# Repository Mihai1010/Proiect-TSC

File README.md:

# Proiect InkTime

**Autor:** Necula Mihai 331 AB

---

## 1. Diagramă Bloc

---

## 2. Bill of Materials (BOM)

| Categorie | Capsulă | Denumire Schematic | JLC | Datasheet |
| :--- | :--- | :--- | :--- | :--- |
| **Capacitors** | **0201** | C1, C2, C3, C4, C5, C7, C8, C9, C11, C12, C13, C16, C17, C18, C19, C22, C23, C27, C29, C30, C31, C32, C34, C37, C38, C42, EPD_C5 | [JLCPCB](https://jlcpcb.com/partdetail/16204-CL05A106MQ5NUNC/C15525) | [DataSheet](https://www.jotrin.jp/userfiles/downloadfile/CL05A106MQ5NUNC/CL05A106MQ5NUNC.pdf) |
| | **0402** | C6, C14, C15, C20, C21, C24, C25, C33, C39, C43, EPD_C1, EPD_C2, EPD_C6, EPD_C7, EPD_C8, EPD_C9, EPD_C10, EPD_C11, EPD_C12, C2-EP-DR1 | [JLCPCB](https://jlcpcb.com/partdetail/C9900006337) | [DataSheet](https://jlcpcb.com/parts) |
| **Resistors** | **0201** | R2, R3, R4, R5, R7, R8, R9, R17, R18, R_TYPE_SEL, R1_EP_DR, R2_EP_DR, R2_PWR_EPD, R1_USB, R2_USB | [JLCPCB](https://jlcpcb.com/partdetail/26484-0402WGF1003TCE/C25741) | [DataSheet](https://www.royalohm.com/assets/pdf/products/smd/1.pdf) |
| **Inductors** | **0402** | L1, L2, L3 | [JLCPCB](https://jlcpcb.com/partdetail/6763488-FTC252012SR47MBCA/C5832368) | [DataSheet](https://www.lcsc.com/datasheet/C5832368.pdf) |
| | **SMD** | L5, L7 | [JLCPCB](https://jlcpcb.com/partdetail/Walsin_TechCorp-WR06X60R4FTL/C168340) | [DataSheet](https://eu.mouser.com/datasheet/3/317/1/ASC_WR.pdf) |
| **ICs** | **BGA/WLCSP** | U1 (nRF52840) | [JLCPCB](https://jlcpcb.com/partdetail/NordicSemicon-NRF52840_QIAAR/C190794) | [DataSheet](https://mm.digikey.com/Volume0/opasdata/d220001/medias/docus/6470/NRF52840-QIAA-R.pdf) |
| | **BGA/WLCSP** | IC1 (BQ25180YBGR) | [JLCPCB](https://jlcpcb.com/partdetail/TexasInstruments-BQ25180YBGR/C3682423) | [DataSheet](https://www.ti.com/cn/lit/ds/symlink/bq25180.pdf?ts=1776165850601) |
| | **BGA/WLCSP** | IC2 (DRV2605YZFR) | [JLCPCB](https://jlcpcb.com/partdetail/TexasInstruments-DRV2605YZFR/C81079) | [DataSheet](https://www.ti.com/cn/lit/ds/symlink/drv2605.pdf?ts=1776155639464&ref_url=https%253A%252F%252Fso.szlcsc.com%252F) |
| | **BGA/WLCSP** | IC9 (RT6160AWSC) | [JLCPCB](https://jlcpcb.com/partdetail/RichtekTech-RT6160AWSC/C7065276) | [DataSheet](https://www.alldatasheet.com/datasheet-pdf/pdf/1709403/RICHTEK/RT6160AWSC.html) |
| | **LGA** | IC3 (BMA421) | [JLCPCB](https://jlcpcb.com/partdetail/BoschSensortec-BMA421/C5242966) | [DataSheet](https://www.alldatasheet.com/datasheet-pdf/pdf/1137426/BOSCH/BMA421.html) |
| | **SON/TDFN** | U3 (MAX17048) | [JLCPCB](https://jlcpcb.com/partdetail/2777647-MAX17048GT10/C2682616) | [DataSheet](https://www.analog.com/media/en/technical-documentation/data-sheets/MAX17048-MAX17049.pdf) |
| **Diodes/FETs** | **SOD-123** | D2, D4, D5 | [JLCPCB](https://jlcpcb.com/partdetail/ST_Semtech-1N4148W/C81598) | [DataSheet](https://www.mccsemi.com/pdf/Products/1N4148W(SOD-123).pdf) |
| | **SOT-23** | Q1 (DMG2305) | [JLCPCB](https://jlcpcb.com/partdetail/TECHPUBLIC-DMG2305UX/C2940629) | [DataSheet](https://www.mouser.com/datasheet/2/115/DMG2305UX-266242.pdf) |
| | **SOT-323** | Q3 (SI1308EDL) | [JLCPCB](https://jlcpcb.com/partdetail/VishayIntertech-SI1308EDL_T1GE3/C469327) | [DataSheet](https://www.vishay.com](https://www.vishay.com/docs/63399/si1308edl.pdf)) |
| | **SOT-23-6** | D3 (USBLC6) | [JLCPCB](https://jlcpcb.com/partdetail/STMicroelectronics-USBLC62SC6/C7519) | [DataSheet](https://www.st.com](https://www.st.com/resource/en/datasheet/usblc6-2.pdf)) |
| **Connectors** | **FPC 24** | J1 | [JLCPCB](https://jlcpcb.com/partdetail/MOLEX-5034802400/C122434) | [DataSheet](https://www.molex.com/content/dam/molex/molex-dot-com/products/automated/en-us/salesdrawingpdf/503/503480/5034802400_sd.pdf?inline) |
| | **USB-C** | J4 | [JLCPCB](https://jlcpcb.com/partdetail/EverlightElec-16_213SDRC_S530_A3TR8/C71911) | [DataSheet](https://www.endrich.com/Datenbl%C3%A4tter/Lichtl%C3%B6sungen/Everlight/Single%20Color%20LED/16-213SDRCS530-A3TR8.pdf) |
| | **Tag-Connect**| J2 (TC2030) | [JLCPCB](https://jlcpcb.com/partdetail/MicrochipTech-TC2030_CLIP3PACK/C5444772) | [DataSheet](https://www.farnell.com/datasheets/2818736.pdf) |
| **User I/O** | **Switch** | SW_DN, SW_ENT, SW_UP | [JLCPCB](https://jlcpcb.com/partdetail/ALPSALPINE-SKRKAEE020/C115357) | [DataSheet](https://www.tme.eu/Document/305984bf119cfa40f7a209117dc97838/SKRKAEE020.PDF) |
| | **Antenna** | ANT1 | [JLCPCB](https://jlcpcb.com/partdetail/JohansonDielectrics-2450AT18B100E/C2917717) | [DataSheet](https://www.johansontechnology.com/docs/1187/2450AT18B100_X8XXogU.pdf) |
| | **Oscillator** | X1, X2 | [JLCPCB](https://jlcpcb.com/partdetail/STMicroelectronics-BALNRF01D3/C87765) | [DataSheet](https://www.st.com/resource/en/datasheet/bal-nrf01d3.pdf) |
| **Mechanical** | **Custom** | Baterie, Display, Shaker | - | [Mechanical Folder](./Mechanical) |

---

## 3. Descrierea Funcționalității Hardware

### 3.1 Unitatea Centrală de Procesare (MCU)
Nucleul dispozitivului este **Nordic nRF52840**. 
* Dispune de un procesor pe 32 de biți la 64 MHz, capabil să gestioneze algoritmi complecși și procesare de semnal.
* Utilizează un oscilator de **32 MHz** pentru operarea nucleului și a radioului.

### 3.2 Energie și Alimentare
* **LiPo Charger (BQ25180):** Gestionează procesul de încărcare al bateriei de 250mAh prin interfața USB-C.
* **Fuel Gauge (MAX17048):** Oferă monitorizare precisă a stării de încărcare și a tensiunii bateriei.
* **Convertor DC/DC (RT6160A):** Un convertor care transformă tensiunea variabilă a bateriei într-o tensiune stabilă de **3.3V**.

### 3.3 Senzori și Interfețe de Comunicare
* **IMU (BMA421):** Accelerometru triaxial ultra-low power folosit pentru detectarea pașilor și a gesturilor de activare a ecranului.
* **Haptic Driver (DRV2605):** Driver specializat pentru controlul Shaker-ului.
* **Display (Waveshare 1.54"):** O rezoluție de 200x200px. Acesta păstrează imaginea fără a consuma curent, activând circuitul de drive doar în timpul împrospătării (refresh).

### 3.4 Specificații de Comunicație
* **Protocol:** Bluetooth 5.0 Low Energy.
* **Antenă:** Antenă 2450AT18B100E la 2.4GHz.

### 3.5 Consum de Energie
* **System OFF:** aprox. 25 µA.
* **Standby:** aprox. 150 µA.
* **Display Refresh:** aprox. 10 mA.

---

## 4 Alocarea Pinilor nRF52840

| Componentă | Interfață | Pini | Explicație |
| :--- | :--- | :--- | :--- |
| **I2C Bus** | I2C | P0.26 (SDA), P0.27 (SCL) | Magistrală partajată: IMU, Gauge, Haptic, Charger. |
| **E-Paper** | SPI | P0.20 (SCK), P0.24 (MOSI), P0.22 (MISO) | Interfață pentru datele de imagine. |
| **E-Paper Ctrl** | GPIO | P0.17 (CS), P0.19 (D/C), P0.13 (BUSY) | Pini dedicați pentru controlul stării driver-ului display-ului. |
| **Buttons** | GPIO | P0.11 (UP), P0.12 (ENT), P0.25 (DN) | Configurați cu pull-up intern pentru detectarea apăsărilor. |
| **Haptic/PWM** | PWM/I2C | P0.14 (INT/Trigger) | Declanșare hardware a efectelor haptice. |
| **SWD** | Debug | SWDIO, SWDCLK, RESET | Programare și debug via conectorul TC2030. |

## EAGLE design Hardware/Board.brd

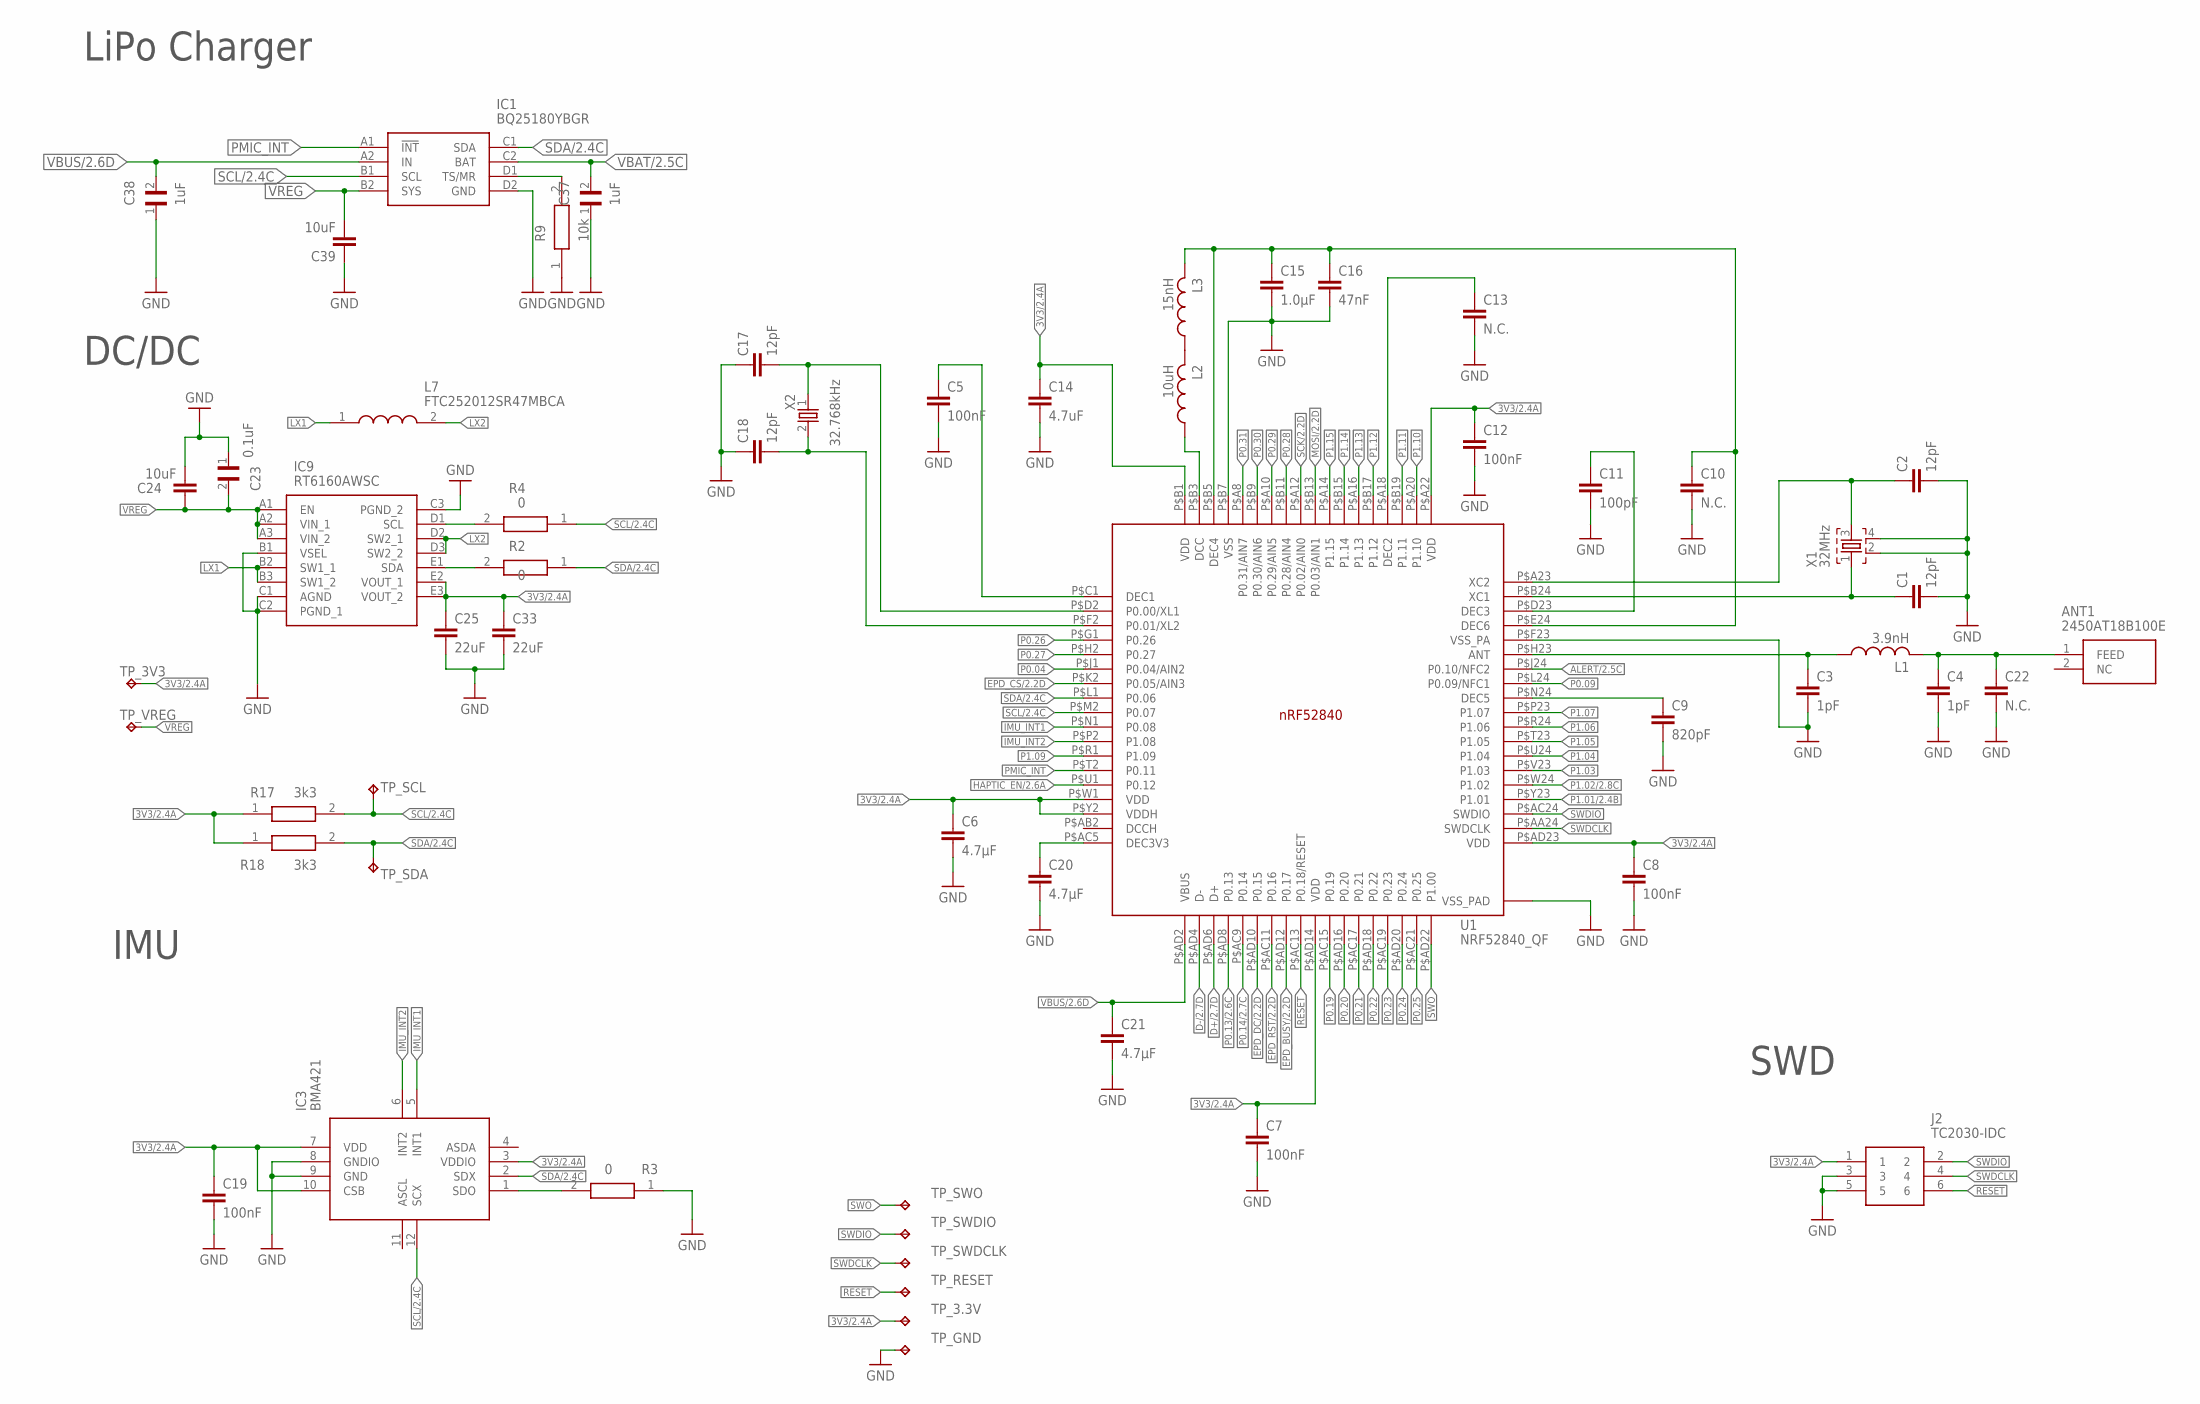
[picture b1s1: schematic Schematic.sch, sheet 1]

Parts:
ANT1: 2450AT18B100E; 2450AT18B100E_ANTC3216X140N
C1, C2, C17, C18: 12pF; NORDIC_NRF_3_RESC0201_L
C3, C4: 1pF; NORDIC_NRF_3_RESC0201_L
C5, C7, C8, C12, C19: 100nF; NORDIC_NRF_3_RESC0201_L
C6, C20, C21: 4.7µF; PERFECT_0402_0402
C9: 820pF; NORDIC_NRF_3_RESC0201_L
C10, C13, C22: N.C.; NORDIC_NRF_3_RESC0201_L
C11: 100pF; NORDIC_NRF_3_RESC0201_L
C14: 4.7uF; PERFECT_0402_0402
C15: 1.0µF; PERFECT_0402_0402
C16: 47nF; NORDIC_NRF_3_RESC0201_L
C23: 0.1uF; GRM011R60J152KE01L_2_CAPC0201X13N
C24, C39: 10uF; PERFECT_0402_0402
C25, C33: 22uF; PERFECT_0402_0402
C37, C38: 1uF; GRM011R60J152KE01L_2_CAPC0201X13N
IC1: BQ25180YBGR; BQ25180YBGR_BGA8C40P2X4_100X155X50
IC3: BMA421; BMA423_BMA423
IC9: RT6160AWSC; RT6160AWSC_BGA15C40P3X5_140X230X60
J2: TC2030-IDC; TC2030-IDC_TC2030IDC
L1: 3.9nH; NORDIC_NRF_2_RESC0402_L
L2: 10uH; NORDIC_NRF_2_RESC0402_L
L3: 15nH; NORDIC_NRF_2_RESC0402_L
L7: FTC252012SR47MBCA; MLP2016SR47MT0S1_INDC2016X100N
R2, R3, R4: 0; CPF0201D7K68C1_0201
R9: 10k; CPF0201D7K68C1_0201
R17, R18: 3k3; CPF0201D7K68C1_0201
TP_3.3V, TP_3V3: HECTOR_WATCH_1_TPTP20R; HECTOR_WATCH_1_TP20R
TP_GND: HECTOR_WATCH_1_TPTP20R; HECTOR_WATCH_1_TP20R
TP_RESET: HECTOR_WATCH_1_TPTP20R; HECTOR_WATCH_1_TP20R
TP_SCL: HECTOR_WATCH_1_TPTP20R; HECTOR_WATCH_1_TP20R
TP_SDA: HECTOR_WATCH_1_TPTP20R; HECTOR_WATCH_1_TP20R
TP_SWDCLK: HECTOR_WATCH_1_TPTP20R; HECTOR_WATCH_1_TP20R
TP_SWDIO: HECTOR_WATCH_1_TPTP20R; HECTOR_WATCH_1_TP20R
TP_SWO: HECTOR_WATCH_1_TPTP20R; HECTOR_WATCH_1_TP20R
TP_VREG: HECTOR_WATCH_1_TPTP20R; HECTOR_WATCH_1_TP20R
U1: NRF52840_QF; NORDIC_NRF_4_AQFN50P700X700X85_HS-74N
X1: 32MHz; NORDIC_NRF_BT-XTAL_2016_N
X2: 32.768kHz; NORDIC_NRF_1_XTAL_3215_N

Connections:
3V3/2.4A: C6.1, C7.1, C8.1, C12.1, C14.1, C19.1, C25.1, C33.1, IC3.3 (VDDIO), IC3.7 (VDD), IC3.10 (CSB), IC9.E2 (VOUT_1), IC9.E3 (VOUT_2), J2.1, R17.1, R18.1, TP_3.3V.TP, TP_3V3.TP, U1.P$A22 (VDD), U1.P$AD14 (VDD), U1.P$AD23 (VDD), U1.P$B1 (VDD), U1.P$W1 (VDD), U1.P$Y2 (VDDH)
ALERT/2.5C: U1.P$J24 (P0.10/NFC2)
D+/2.7D: U1.P$AD6 (D+)
D-/2.7D: U1.P$AD4 (D-)
EPD_BUSY/2.2D: U1.P$AD12 (P0.17)
EPD_CS/2.2D: U1.P$K2 (P0.05/AIN3)
EPD_DC/2.2D: U1.P$AD10 (P0.15)
EPD_RST/2.2D: U1.P$AC11 (P0.16)
GND: C1.2, C2.2, C3.2, C4.2, C5.2, C6.2, C7.2, C8.2, C9.2, C10.2, C11.2, C12.2, C13.2, C14.2, C15.2, C16.2, C17.1, C18.1, C19.2, C20.2, C21.2, C22.2, C23.1, C24.2, C25.2, C33.2, C37.1, C38.1, C39.1, IC1.D2 (GND), IC3.8 (GNDIO), IC3.9 (GND), IC9.B1 (VSEL), IC9.C1 (AGND), IC9.C2 (PGND_1), IC9.C3 (PGND_2), J2.3, J2.5, R3.1, R9.1, TP_GND.TP, U1.P$74 (VSS_PAD), U1.P$75 (VSS_PAD), U1.P$76 (VSS_PAD), U1.P$77 (VSS_PAD), U1.P$78 (VSS_PAD), U1.P$79 (VSS_PAD), U1.P$80 (VSS_PAD), U1.P$81 (VSS_PAD), U1.P$82 (VSS_PAD), U1.P$83 (VSS_PAD), U1.P$84 (VSS_PAD), U1.P$85 (VSS_PAD), U1.P$86 (VSS_PAD), U1.P$87 (VSS_PAD), U1.P$88 (VSS_PAD), U1.P$89 (VSS_PAD), U1.P$90 (VSS_PAD), U1.P$B7 (VSS), U1.P$F23 (VSS_PA), X1.2, X1.4; also elsewhere on the board
HAPTIC_EN/2.6A: U1.P$U1 (P0.12)
IMU_INT1: IC3.5 (INT1), U1.P$N1 (P0.08)
IMU_INT2: IC3.6 (INT2), U1.P$P2 (P1.08)
LX1: IC9.B2 (SW1_1), IC9.B3 (SW1_2), L7.1
LX2: IC9.D2 (SW2_1), IC9.D3 (SW2_2), L7.2
MOSI/2.2D: U1.P$B13 (P0.03/AIN1)
unnamed: C5.1, U1.P$C1 (DEC1)
unnamed: IC9.D1 (SCL), R4.2
unnamed: IC1.D1 (TS/MR), R9.2
unnamed: C20.1, U1.P$AC5 (DEC3V3)
unnamed: IC9.E1 (SDA), R2.2
unnamed: C17.2, U1.P$D2 (P0.00/XL1), X2.1
unnamed: ANT1.1 (FEED), C4.1, C22.1, L1.2
unnamed: IC3.1 (SDO), R3.2
unnamed: C18.2, U1.P$F2 (P0.01/XL2), X2.2
unnamed: C13.1, U1.P$A18 (DEC2)
unnamed: L2.1, U1.P$B3 (DCC)
unnamed: L2.2, L3.1
unnamed: C9.1, U1.P$N24 (DEC5)
unnamed: C3.1, L1.1, U1.P$H23 (ANT)
unnamed: C10.1, C15.1, C16.1, L3.2, U1.P$B5 (DEC4), U1.P$E24 (DEC6)
unnamed: C11.1, U1.P$D23 (DEC3)
unnamed: C1.1, U1.P$B24 (XC1), X1.1
unnamed: C2.1, U1.P$A23 (XC2), X1.3
P0.04: U1.P$J1 (P0.04/AIN2)
P0.09: U1.P$L24 (P0.09/NFC1)
P0.13/2.6C: U1.P$AD8 (P0.13)
P0.14/2.7C: U1.P$AC9 (P0.14)
P0.19: U1.P$AC15 (P0.19)
P0.20: U1.P$AD16 (P0.20)
P0.21: U1.P$AC17 (P0.21)
P0.22: U1.P$AD18 (P0.22)
P0.23: U1.P$AC19 (P0.23)
P0.24: U1.P$AD20 (P0.24)
P0.25: U1.P$AC21 (P0.25)
P0.26: U1.P$G1 (P0.26)
P0.27: U1.P$H2 (P0.27)
P0.28: U1.P$B11 (P0.28/AIN4)
P0.29: U1.P$A10 (P0.29/AIN5)
P0.30: U1.P$B9 (P0.30/AIN6)
P0.31: U1.P$A8 (P0.31/AIN7)
P1.01/2.4B: U1.P$Y23 (P1.01)
P1.02/2.8C: U1.P$W24 (P1.02)
P1.03: U1.P$V23 (P1.03)
P1.04: U1.P$U24 (P1.04)
P1.05: U1.P$T23 (P1.05)
P1.06: U1.P$R24 (P1.06)
P1.07: U1.P$P23 (P1.07)
P1.09: U1.P$R1 (P1.09)
P1.10: U1.P$A20 (P1.10)
P1.11: U1.P$B19 (P1.11)
P1.12: U1.P$B17 (P1.12)
P1.13: U1.P$A16 (P1.13)
P1.14: U1.P$B15 (P1.14)
P1.15: U1.P$A14 (P1.15)
PMIC_INT: IC1.A1 (!INT), U1.P$T2 (P0.11)
RESET: J2.6, TP_RESET.TP, U1.P$AC13 (P0.18/RESET)
SCK/2.2D: U1.P$A12 (P0.02/AIN0)
SCL/2.4C: IC1.B1 (SCL), IC3.12 (SCX), R4.1, R17.2, TP_SCL.TP, U1.P$M2 (P0.07)
SDA/2.4C: IC1.C1 (SDA), IC3.2 (SDX), R2.1, R18.2, TP_SDA.TP, U1.P$L1 (P0.06)
SWDCLK: J2.4, TP_SWDCLK.TP, U1.P$AA24 (SWDCLK)
SWDIO: J2.2, TP_SWDIO.TP, U1.P$AC24 (SWDIO)
SWO: TP_SWO.TP, U1.P$AD22 (P1.00)
VBAT/2.5C: C37.2, IC1.C2 (BAT)
VBUS/2.6D: C21.1, C38.2, IC1.A2 (IN), U1.P$AD2 (VBUS)
VREG: C23.2, C24.1, C39.2, IC1.B2 (SYS), IC9.A1 (EN), IC9.A2 (VIN_1), IC9.A3 (VIN_2), TP_VREG.TP

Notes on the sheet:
LiPo Charger
DC/DC
IMU
SWD

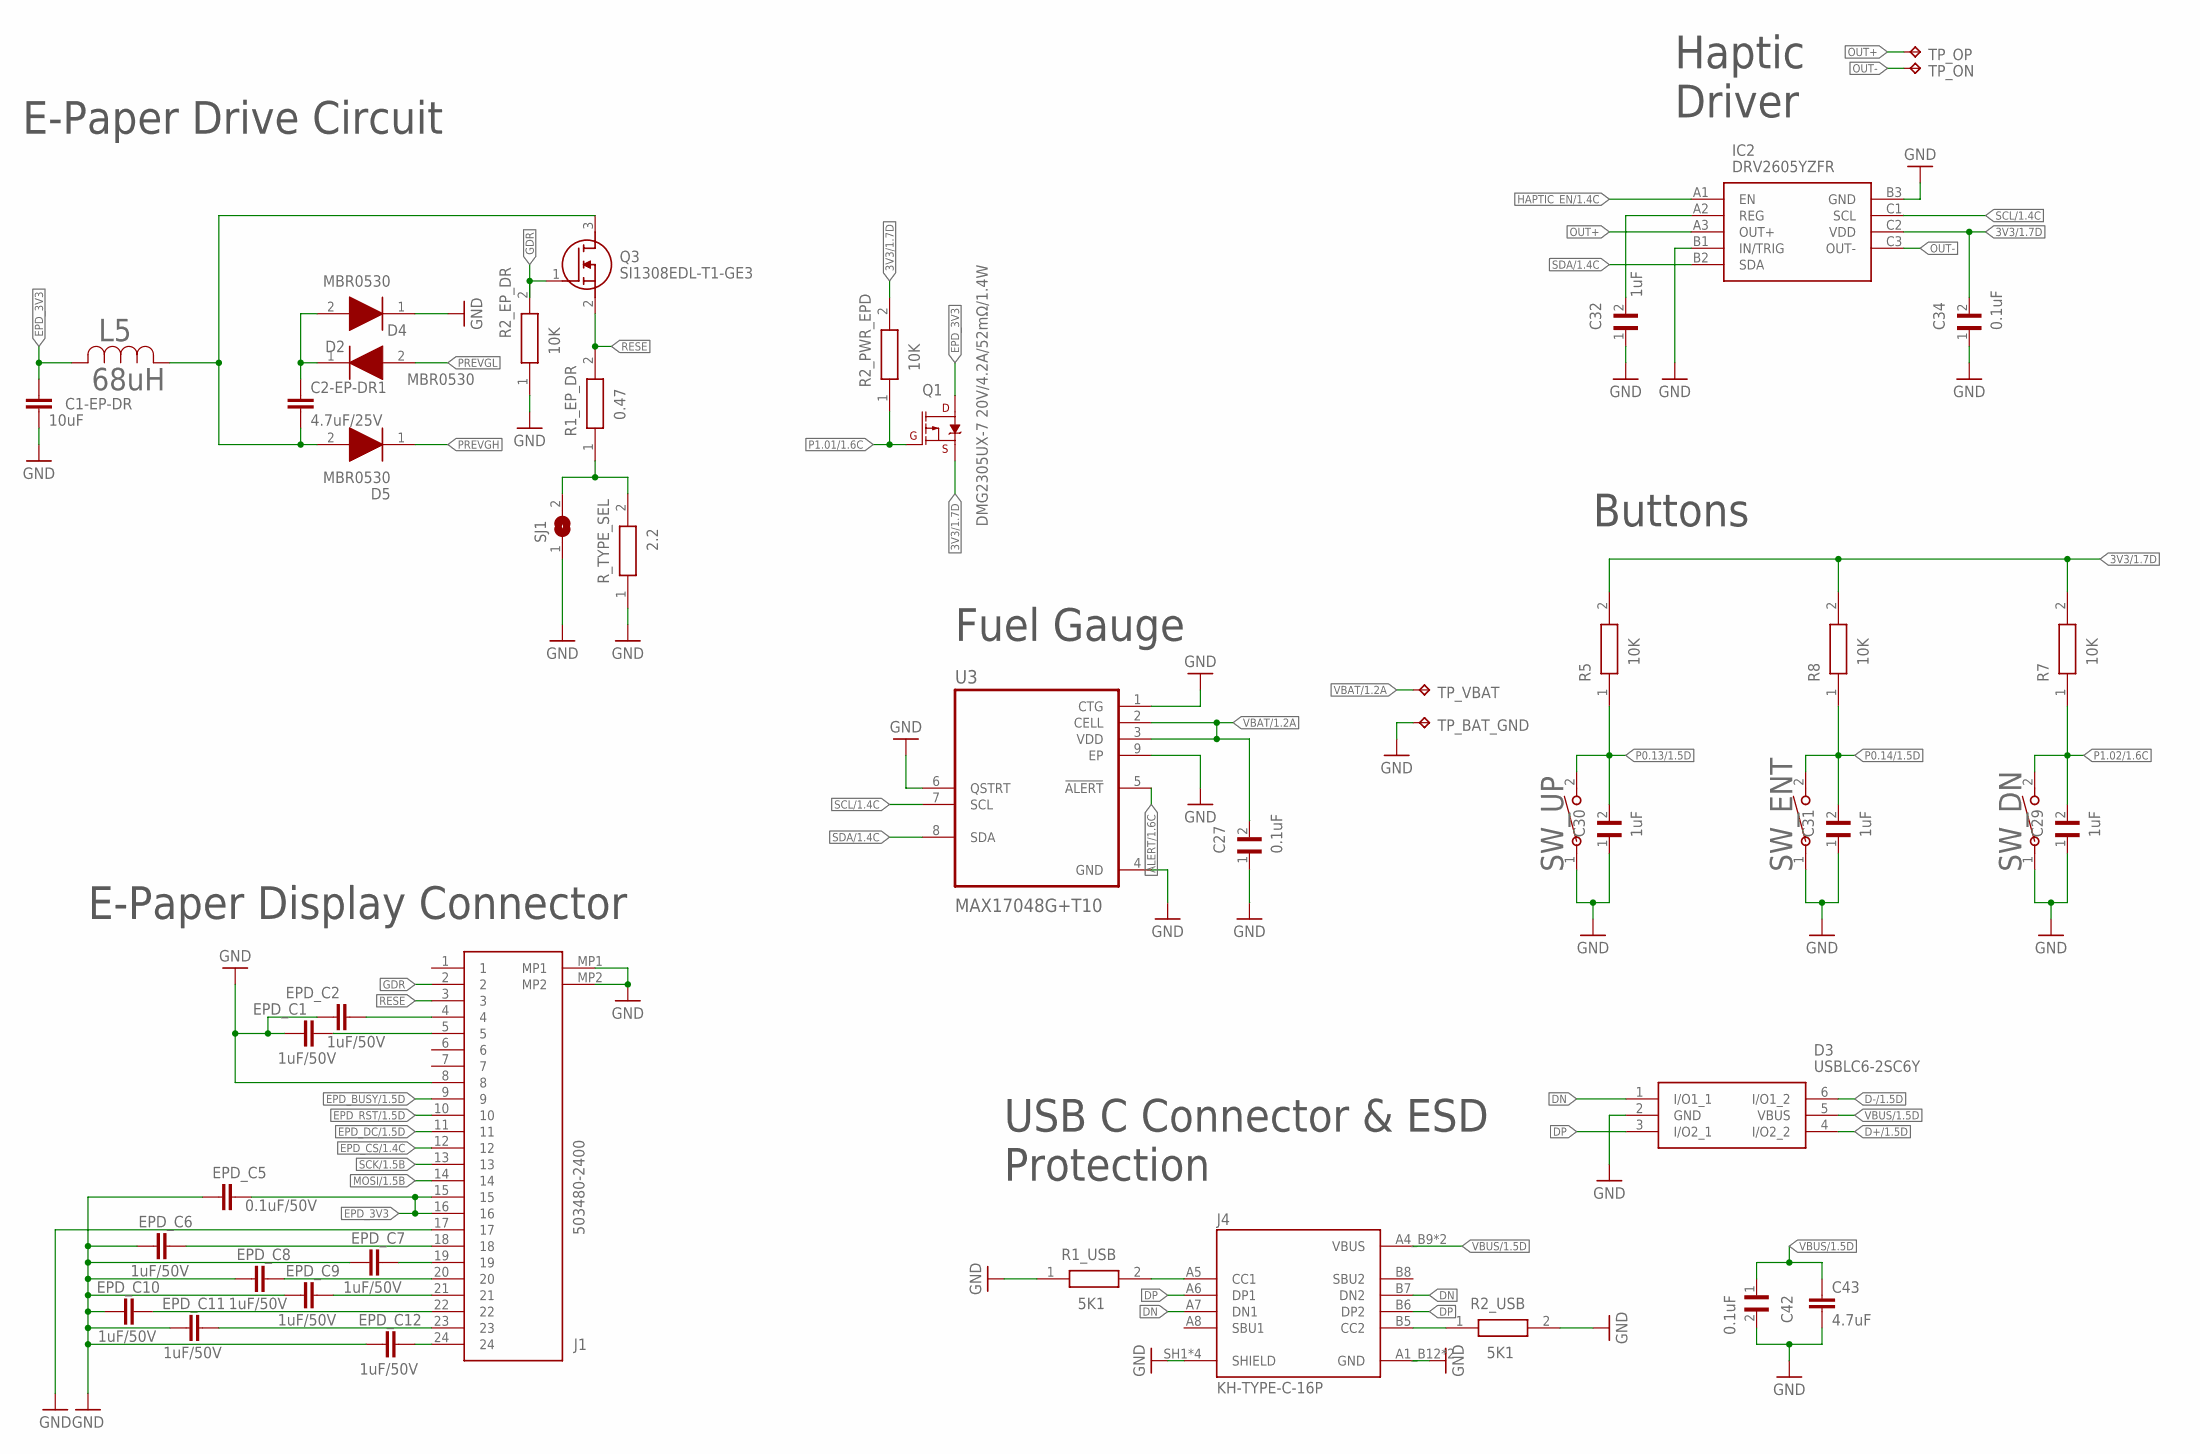
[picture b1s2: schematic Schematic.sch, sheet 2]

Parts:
C1-EP-DR: 10uF; PERFECT_0402_0402
C2-EP-DR1: 4.7uF/25V; PERFECT_0402_0402
C27, C34, C42: 0.1uF; GRM011R60J152KE01L_2_CAPC0201X13N
C29, C30, C31, C32: 1uF; GRM011R60J152KE01L_2_CAPC0201X13N
C43: 4.7uF; PERFECT_0402_0402
D2, D4, D5: MBR0530; ESP32_C6_LIBRARY_5_SOD3716X135N
D3: USBLC6-2SC6Y; ESP32_C6_LIBRARY_3_SOT95P280X145-6N
EPD_C1, EPD_C2, EPD_C6, EPD_C7, EPD_C8, EPD_C9, EPD_C10, EPD_C11, EPD_C12: 1uF/50V; PERFECT_0402_0402
EPD_C5: 0.1uF/50V; NORDIC_NRF_3_RESC0201_L
IC2: DRV2605YZFR; DRV2605YZFR_BGA9C50P3X3_144X144X62
J1: 503480-2400; 503480-2400_5034802400
J4: KH-TYPE-C-16P; KH-TYPE-C-16P_KINGHELM_KH-TYPE-C-16P
L5: 68uH; ESP32_C6_LIBRARY_2_IND_4828-WE-TPC_WRE
Q1: DMG2305UX-7 20V/4.2A/52mΩ/1.4W; ESP32_C6_LIBRARY_4_ESP32_C6_LIBRARY_4_ESP32_C6_LIBRARY_4_ES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
Q3: SI1308EDL-T1-GE3; ESP32_C6_LIBRARY_6_SOT65P210X110-3N
R1_EP_DR: 0.47; CPF0201D7K68C1_0201
R1_USB, R2_USB: 5K1; CPF0201D7K68C1_0201
R2_EP_DR, R2_PWR_EPD, R5, R7, R8: 10K; CPF0201D7K68C1_0201
R_TYPE_SEL: 2.2; CPF0201D7K68C1_0201
SJ1: ESP32_C6_LIBRARY_7_JUMPER_SJ
SW_DN: 2025-10-22_07-23-44_LIBRARY_EVP-AKE31ASW_EVP-AKE3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; 2025-10-22_07-23-44_LIBRARY_SW_EVP-AKE31A_PAN
SW_ENT: 2025-10-22_07-23-44_LIBRARY_EVP-AKE31ASW_EVP-AKE3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; 2025-10-22_07-23-44_LIBRARY_SW_EVP-AKE31A_PAN
SW_UP: 2025-10-22_07-23-44_LIBRARY_EVP-AKE31ASW_EVP-AKE3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; 2025-10-22_07-23-44_LIBRARY_SW_EVP-AKE31A_PAN
TP_BAT_GND: HECTOR_WATCH_1_TPTP20R; HECTOR_WATCH_1_TP20R
TP_ON: HECTOR_WATCH_1_TPTP20R; HECTOR_WATCH_1_TP20R
TP_OP: HECTOR_WATCH_1_TPTP20R; HECTOR_WATCH_1_TP20R
TP_VBAT: HECTOR_WATCH_1_TPTP20R; HECTOR_WATCH_1_TP20R
U3: MAX17048G+T10; ESP32_C6_LIBRARY_SON50P200X200X80-9N

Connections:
3V3/1.7D: C34.2, IC2.C2 (VDD), Q1.2 (S), R2_PWR_EPD.2, R5.2, R7.2, R8.2
ALERT/1.6C: U3.5 (!ALERT)
D+/1.5D: D3.4 (I/O2_2)
D-/1.5D: D3.6 (I/O1_2)
DN: D3.1 (I/O1_1), J4.A7 (DN1), J4.B7 (DN2)
DP: D3.3 (I/O2_1), J4.A6 (DP1), J4.B6 (DP2)
EPD_3V3: C1-EP-DR.1, EPD_C5.2, J1.15, J1.16, L5.2, Q1.3 (D)
EPD_BUSY/1.5D: J1.9
EPD_CS/1.4C: J1.12
EPD_DC/1.5D: J1.11
EPD_RST/1.5D: J1.10
GDR: J1.2, Q3.1 (G), R2_EP_DR.2
GND: C1-EP-DR.2, C27.1, C29.1, C30.1, C31.1, C32.1, C34.1, C42.2, C43.2, D3.2 (GND), D4.1 (K), EPD_C1.1, EPD_C2.1, EPD_C5.1, EPD_C6.1, EPD_C7.1, EPD_C8.1, EPD_C9.1, EPD_C10.1, EPD_C11.1, EPD_C12.1, IC2.B1 (IN/TRIG), IC2.B3 (GND), J1.8, J1.17, J1.MP1, J1.MP2, J4.A1_B12 (GND), J4.A12_B1 (GND), J4.SH1 (SHIELD), J4.SH2 (SHIELD), J4.SH3 (SHIELD), J4.SH4 (SHIELD), R1_USB.1, R2_EP_DR.1, R2_USB.2, R_TYPE_SEL.1, SJ1.1, SW_DN.1, SW_ENT.1, SW_UP.1, TP_BAT_GND.TP, U3.1 (CTG), U3.4 (GND), U3.6 (QSTRT), U3.9 (EP); also elsewhere on the board
HAPTIC_EN/1.4C: IC2.A1 (EN)
MOSI/1.5B: J1.14
unnamed: C2-EP-DR1.1, D2.1 (K), D4.2 (A)
unnamed: C2-EP-DR1.2, D5.2 (A), L5.1, Q3.3 (D)
unnamed: EPD_C6.2, J1.18
unnamed: EPD_C2.2, J1.4
unnamed: R1_EP_DR.1, R_TYPE_SEL.2, SJ1.2
unnamed: EPD_C1.2, J1.5
unnamed: EPD_C7.2, J1.19
unnamed: EPD_C8.2, J1.20
unnamed: EPD_C9.2, J1.21
unnamed: J4.B5 (CC2), R2_USB.1
unnamed: J4.A5 (CC1), R1_USB.2
unnamed: C32.2, IC2.A2 (REG)
unnamed: EPD_C10.2, J1.22
unnamed: EPD_C11.2, J1.23
unnamed: EPD_C12.2, J1.24
OUT+: IC2.A3 (OUT+), TP_OP.TP
OUT-: IC2.C3 (OUT-), TP_ON.TP
P0.13/1.5D: C30.2, R5.1, SW_UP.2
P0.14/1.5D: C31.2, R8.1, SW_ENT.2
P1.01/1.6C: Q1.1 (G), R2_PWR_EPD.1
P1.02/1.6C: C29.2, R7.1, SW_DN.2
PREVGH: D5.1 (K)
PREVGL: D2.2 (A)
RESE: J1.3, Q3.2 (S), R1_EP_DR.2
SCK/1.5B: J1.13
SCL/1.4C: IC2.C1 (SCL), U3.7 (SCL)
SDA/1.4C: IC2.B2 (SDA), U3.8 (SDA)
VBAT/1.2A: C27.2, TP_VBAT.TP, U3.2 (CELL), U3.3 (VDD)
VBUS/1.5D: C42.1, C43.1, D3.5 (VBUS), J4.A4_B9 (VBUS), J4.A9_B4 (VBUS)

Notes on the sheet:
E-Paper Drive Circuit
Haptic Driver
Buttons
Fuel Gauge
E-Paper Display Connector
USB C Connector & ESD Protection

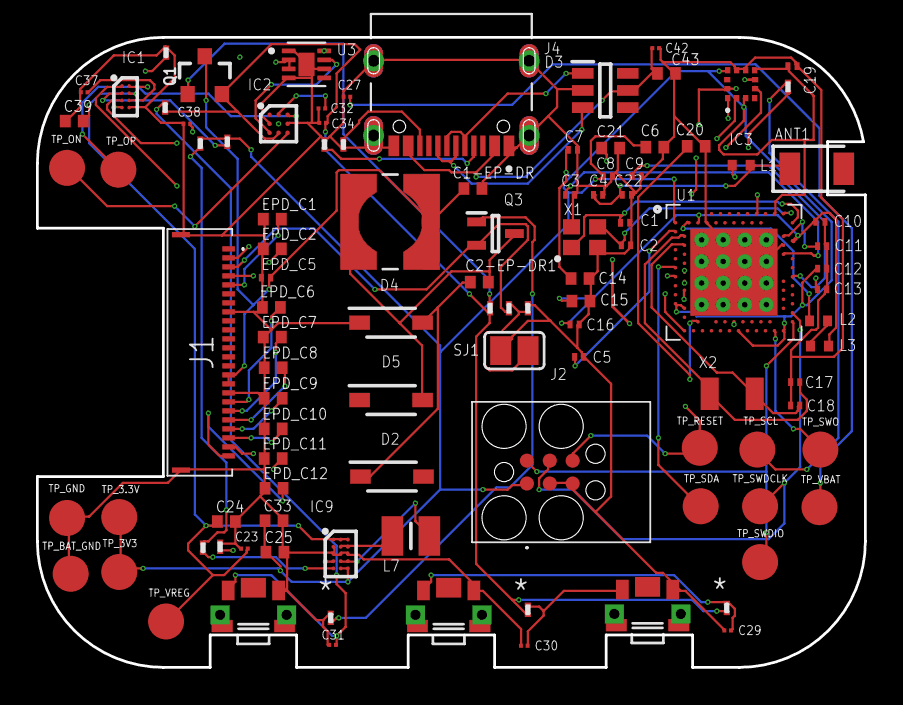
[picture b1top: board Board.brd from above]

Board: 4 copper layers, 46.0 x 35.0 mm, 105 parts (0 on the bottom side), 65 nets.

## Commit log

2026-04-10 load
2026-04-15 Rename Block Diagram.png to block_diagram.png
2026-04-15 final

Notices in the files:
parts and their libraries:
COPYRIGHT: Copyright (C) 2024 Ultra Librarian. All rights reserved.
COPYRIGHT: Copyright (C) 2025 Ultra Librarian. All rights reserved.
